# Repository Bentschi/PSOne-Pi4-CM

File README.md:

## Introduction
The goal of this project is to create open source hardware and software that replaces parts of a PSOne console mainly with a Raspbery PI 4 Compute Module, while remaining the beauty of the console and most of the functionality.
That means you would be able to use your playstation dualshock controllers, the memory card slots, and if i can get it to work the cd drive aswell.

## Raspberry Pi 4 Compute Module - the heart
As mentioned it will be mainly powered by a Raspberry PI 4 Compute Module, and i will try to break out as much IO as reasonably possible.
Sadly in a PSOne with a CD drive there is not much room to work with, and I decided for a non-destructive method of routing out the ports.
I want to use the connector U10-A074-361T from Amphenol (also known as Slim SAS, and used mostly in servers).
The connector is not really cheap and a little wider than the AV multi out.
But that is the price to pay to not destroy the case of the console, and if the connector is inset in the existing hole it will fit.
With that connector I will route dual HDMI, the gigabit network interface and USB 2.0 out of the back.
As a power port I will use a USB type C receptacle.
A cable that connects to that connector could look something like the following picture.

Alternatively a hub could be designed with said ports and maybe a few extras like usb hub and sound.

I will also add the barrel plug you find on a PSOne.
To save some cost and precious board space the Dual Shock function will most certainly only be enabled by using this barrel plug.
The original PSOne power supply (7.5V / 2.2A) seems to be enough to power this entire system (estimated-power-consumption.ods), however when using a M.2 SSD I would suggest to use a better power supply like the one for the Playstation 2 slim (8.5V / 5.6A).

The PCIe i want to use for a M.2 card interface. and i would love to split the pcie lane for USB 3.0 aswell, but then again i want to stay in a reasonable price range for the parts.
The M.2 slot will be able to hold up to 22x60mm cards, and for 22x80mm cards there would be about 7mm vertical clearance, since the only place where a M.2 slot would make sense interferes a little bit with the cd drive.
Sadly I needed more room for the internal power supply, so I had to remove the footprint (mounting hole) for 22x110mm cards.

I haven't managed to find a good place for a SD card holder, but i will route out the traces at least and put a footprint somewhere internally.
I will route out the DSI and CSI connectors aswell, even if i don't really see a use inside a console for them.

There will be an internal 4 port USB 2.0 hub from the PIs USB 2.0 interface.
One of these 4 USB lines will be routed through the Slim SAS connector.
2 of these USB 2.0 lines will be broken out to an internal 9-Pin USB Header, like you find on motherboards.
And the last USB 2.0 will be used to connect to a STM32F103 chip, that will interface the PSOne peripherals.

## STM32F103 - the PSOne interface
The intended use of the STM32F103 chip is to read from and write to the PSOne controller ports and memory card slots, and hopefully if i can get it to work the cd drive aswell.

The STM32F103 chip will communicate with the Raspberry PI Compute Module via USB 2.0 and will introduce itself as a compound device.
That means that only one USB line is required, and the STM32F103 will be recognized as multiple devices which would be 2x game controllers, 2x mass storage devices (the memory card slots), a cd drive, and probably a device that controls the PWMs for the power LED (RGB of course) and fan in the console.

I want to use a USB type C receptacle to power the console, and i have the idea that if the console is turned off or the Compute Module is not populated, and the console is plugged into a USB Host device (like a Computer), that the USB from the STM32F103 shall be passed through this USB type C connector, so that it is possible to use the PSOne peripherals on other devices aswell.

I am aware that CD drives are obsolete by todays standards, and that it is not gonna be that easy to interface the cd assembly, since there is no documentation about it or a standard like IDE or SATA used.
But for completeness i would want to have it working. And if i get it working it would be pretty simple to make it read actual Playstation CDs since the copy protection is not too complicated if you have full control over the entire CD assembly anyway.

## Cooling the Compute Module
Realisticly a flat fan like in laptops should probably be used and a shroud should be designed, that the air is taken from above the M.2 slot and pushed over the compute module, and with the shroud then directed to the bottom right vent holes on the console.
A connector for a fan (5V / 1A max), PWM controlled by the STM32 will be available, sharing one of the ULN2003 chips that are mainly used for the CD drive.

## Current status
I am currently working on the design and schematic for the board in KiCad.
I want to get as much done as possible until i order a PCB from that to test everything.

I want to mention that I have repaired a lot of older consoles in the past and I have very good knowledge of how these devices actually work.
And with all that knowledge, together with my very good programming skills, and my passion about old consoles and interrest in electronics, i think i have everything i need to get this project working.
But i have to say, even if i am aware of most of the design rules and guidelines, i have never designed a PCB before that i actually ordered to manufacture.
So this would be my very first.

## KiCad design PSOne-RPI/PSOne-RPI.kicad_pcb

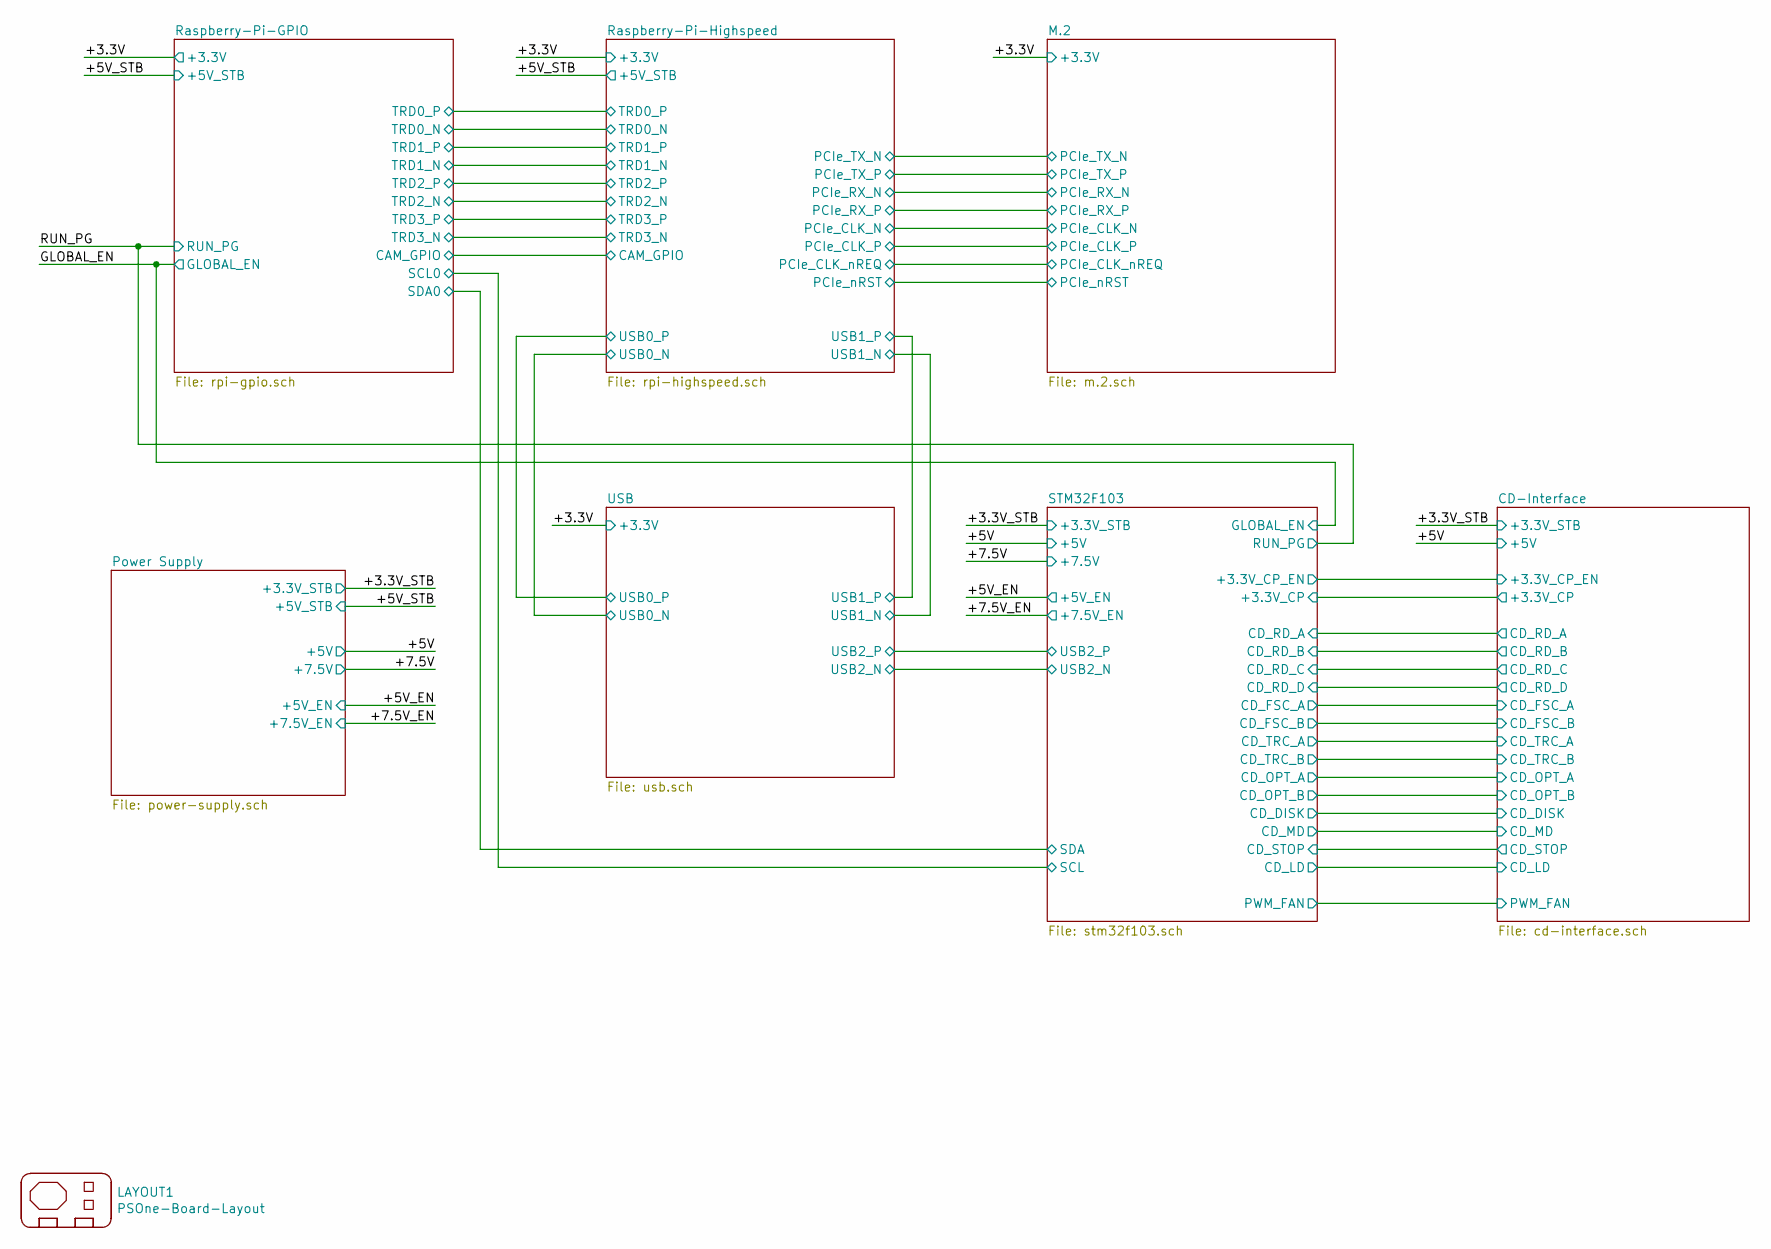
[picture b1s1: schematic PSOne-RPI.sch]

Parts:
LAYOUT1: PSOne-Board-Layout; PSOne-Layout

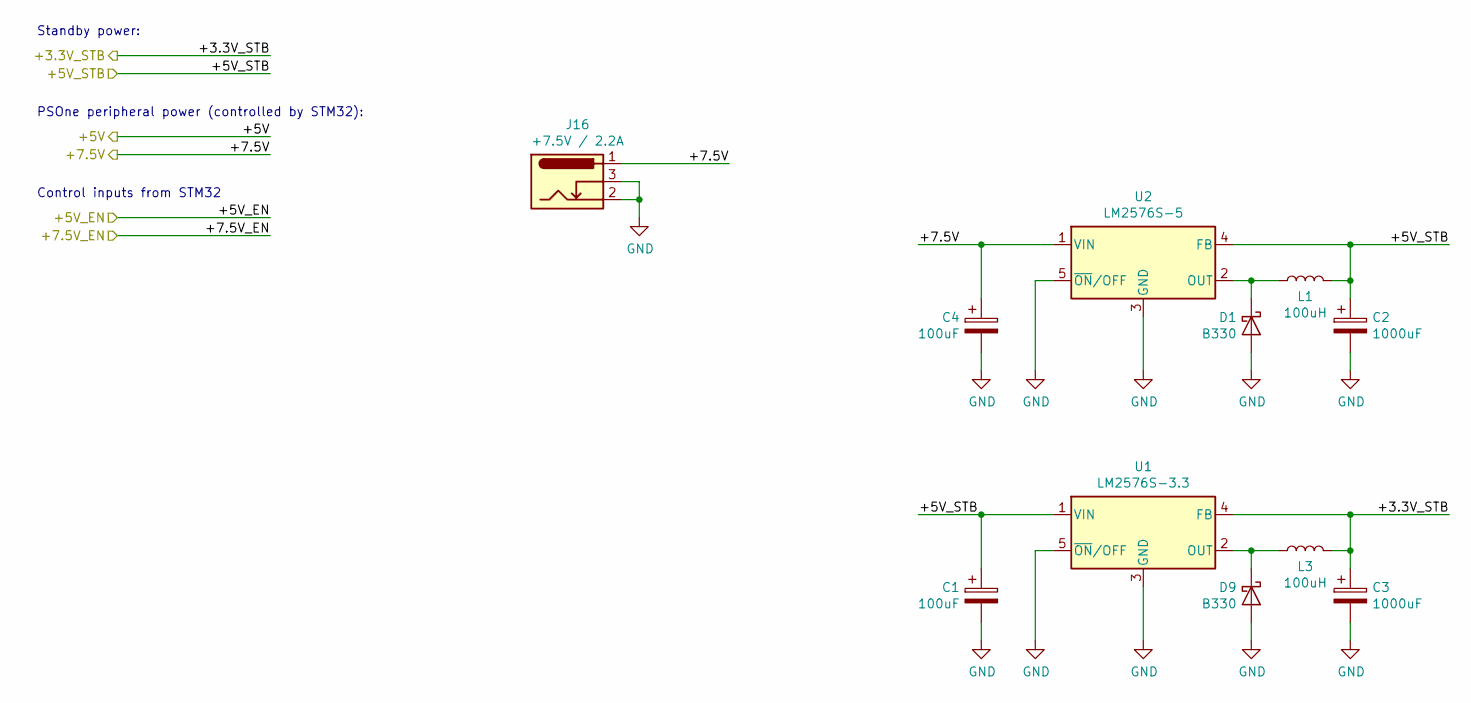
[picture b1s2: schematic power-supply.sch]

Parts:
C1, C4: 100uF; CP_Elec_6.3x5.8
C2, C3: 1000uF; CP_Elec_8x6.5
D1, D9: B330; D_SMC
J16: +7.5V / 2.2A; BarrelJack_Wuerth_6941xx301002
L1, L3: 100uH; L_Bourns_SRR1260
U1: LM2576S-3.3; TO-263-5_TabPin3
U2: LM2576S-5; TO-263-5_TabPin3

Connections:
/+3.3V_STB: C3.1, L3.2, U1.4 (FB); also elsewhere on the board
/+5V_STB: C1.1, C2.1, L1.2, U1.1 (VIN), U2.4 (FB); also elsewhere on the board
/+7.5V: C4.1, J16.1, U2.1 (VIN); also elsewhere on the board
GND: C1.2, C2.2, C3.2, C4.2, D1.2 (A), D9.2 (A), J16.2, J16.3, U1.3 (GND), U1.5 (~ON~/OFF), U2.3 (GND), U2.5 (~ON~/OFF); also elsewhere on the board
unnamed: D1.1 (K), L1.1, U2.2 (OUT)
unnamed: D9.1 (K), L3.1, U1.2 (OUT)

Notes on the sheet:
Standby power:
PSOne peripheral power (controlled by STM32):
Control inputs from STM32

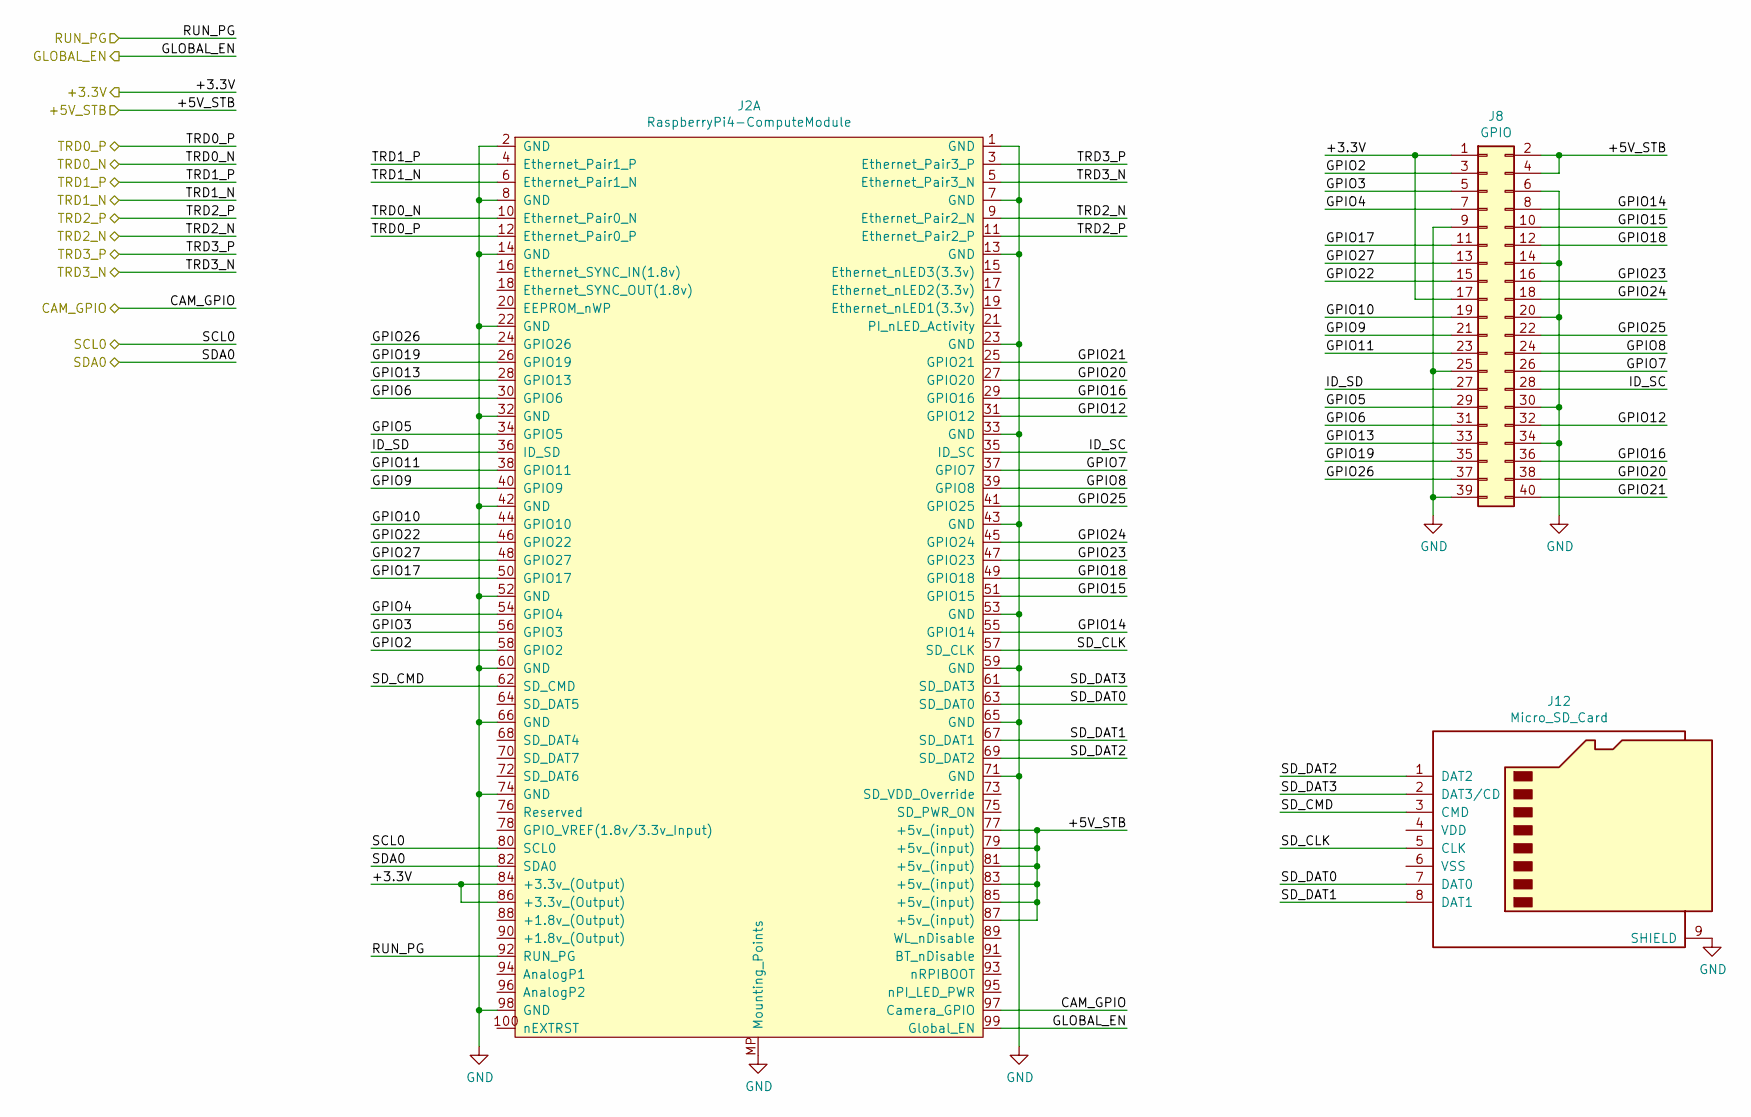
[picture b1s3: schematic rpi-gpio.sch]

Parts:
J2: RaspberryPi4-ComputeModule
J8: GPIO; PinHeader_2x20_P2.54mm_Vertical_SMD
J12: Micro_SD_Card; microSD_HC_Wuerth_693072010801

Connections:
/+3.3V: J2.84 (+3.3v_(Output)), J2.86 (+3.3v_(Output)), J8.1, J8.17; also elsewhere on the board
/+5V_STB: J2.77 (+5v_(input)), J2.79 (+5v_(input)), J2.81 (+5v_(input)), J2.83 (+5v_(input)), J2.85 (+5v_(input)), J2.87 (+5v_(input)), J8.2, J8.4; also elsewhere on the board
/GLOBAL_EN: J2.99 (Global_EN)
/RUN_PG: J2.92 (RUN_PG)
/Raspberry-Pi-GPIO/CAM_GPIO: J2.97 (Camera_GPIO); also elsewhere on the board
/Raspberry-Pi-GPIO/GPIO2: J2.58 (GPIO2), J8.3
/Raspberry-Pi-GPIO/GPIO3: J2.56 (GPIO3), J8.5
/Raspberry-Pi-GPIO/GPIO4: J2.54 (GPIO4), J8.7
/Raspberry-Pi-GPIO/GPIO5: J2.34 (GPIO5), J8.29
/Raspberry-Pi-GPIO/GPIO6: J2.30 (GPIO6), J8.31
/Raspberry-Pi-GPIO/GPIO7: J2.37 (GPIO7), J8.26
/Raspberry-Pi-GPIO/GPIO8: J2.39 (GPIO8), J8.24
/Raspberry-Pi-GPIO/GPIO9: J2.40 (GPIO9), J8.21
/Raspberry-Pi-GPIO/GPIO10: J2.44 (GPIO10), J8.19
/Raspberry-Pi-GPIO/GPIO11: J2.38 (GPIO11), J8.23
/Raspberry-Pi-GPIO/GPIO12: J2.31 (GPIO12), J8.32
/Raspberry-Pi-GPIO/GPIO13: J2.28 (GPIO13), J8.33
/Raspberry-Pi-GPIO/GPIO14: J2.55 (GPIO14), J8.8
/Raspberry-Pi-GPIO/GPIO15: J2.51 (GPIO15), J8.10
/Raspberry-Pi-GPIO/GPIO16: J2.29 (GPIO16), J8.36
/Raspberry-Pi-GPIO/GPIO17: J2.50 (GPIO17), J8.11
/Raspberry-Pi-GPIO/GPIO18: J2.49 (GPIO18), J8.12
/Raspberry-Pi-GPIO/GPIO19: J2.26 (GPIO19), J8.35
/Raspberry-Pi-GPIO/GPIO20: J2.27 (GPIO20), J8.38
/Raspberry-Pi-GPIO/GPIO21: J2.25 (GPIO21), J8.40
/Raspberry-Pi-GPIO/GPIO22: J2.46 (GPIO22), J8.15
/Raspberry-Pi-GPIO/GPIO23: J2.47 (GPIO23), J8.16
/Raspberry-Pi-GPIO/GPIO24: J2.45 (GPIO24), J8.18
/Raspberry-Pi-GPIO/GPIO25: J2.41 (GPIO25), J8.22
/Raspberry-Pi-GPIO/GPIO26: J2.24 (GPIO26), J8.37
/Raspberry-Pi-GPIO/GPIO27: J2.48 (GPIO27), J8.13
/Raspberry-Pi-GPIO/ID_SC: J2.35 (ID_SC), J8.28
/Raspberry-Pi-GPIO/ID_SD: J2.36 (ID_SD), J8.27
/Raspberry-Pi-GPIO/SD_CLK: J2.57 (SD_CLK), J12.5 (CLK)
/Raspberry-Pi-GPIO/SD_CMD: J2.62 (SD_CMD), J12.3 (CMD)
/Raspberry-Pi-GPIO/SD_DAT0: J2.63 (SD_DAT0), J12.7 (DAT0)
/Raspberry-Pi-GPIO/SD_DAT1: J2.67 (SD_DAT1), J12.8 (DAT1)
/Raspberry-Pi-GPIO/SD_DAT2: J2.69 (SD_DAT2), J12.1 (DAT2)
/Raspberry-Pi-GPIO/SD_DAT3: J2.61 (SD_DAT3), J12.2 (DAT3/CD)
/Raspberry-Pi-GPIO/TRD0_N: J2.10 (Ethernet_Pair0_N); also elsewhere on the board
/Raspberry-Pi-GPIO/TRD0_P: J2.12 (Ethernet_Pair0_P); also elsewhere on the board
/Raspberry-Pi-GPIO/TRD1_N: J2.6 (Ethernet_Pair1_N); also elsewhere on the board
/Raspberry-Pi-GPIO/TRD1_P: J2.4 (Ethernet_Pair1_P); also elsewhere on the board
/Raspberry-Pi-GPIO/TRD2_N: J2.9 (Ethernet_Pair2_N); also elsewhere on the board
/Raspberry-Pi-GPIO/TRD2_P: J2.11 (Ethernet_Pair2_P); also elsewhere on the board
/Raspberry-Pi-GPIO/TRD3_N: J2.5 (Ethernet_Pair3_N); also elsewhere on the board
/Raspberry-Pi-GPIO/TRD3_P: J2.3 (Ethernet_Pair3_P); also elsewhere on the board
/STM32F103/SCL: J2.80 (SCL0); also elsewhere on the board
/STM32F103/SDA: J2.82 (SDA0); also elsewhere on the board
GND: J2.1 (GND), J2.2 (GND), J2.7 (GND), J2.8 (GND), J2.13 (GND), J2.14 (GND), J2.22 (GND), J2.23 (GND), J2.32 (GND), J2.33 (GND), J2.42 (GND), J2.43 (GND), J2.52 (GND), J2.53 (GND), J2.59 (GND), J2.60 (GND), J2.65 (GND), J2.66 (GND), J2.71 (GND), J2.74 (GND), J2.98 (GND), J2.MP (Mounting_Points), J8.6, J8.9, J8.14, J8.20, J8.25, J8.30, J8.34, J8.39, J12.9 (SHIELD); also elsewhere on the board

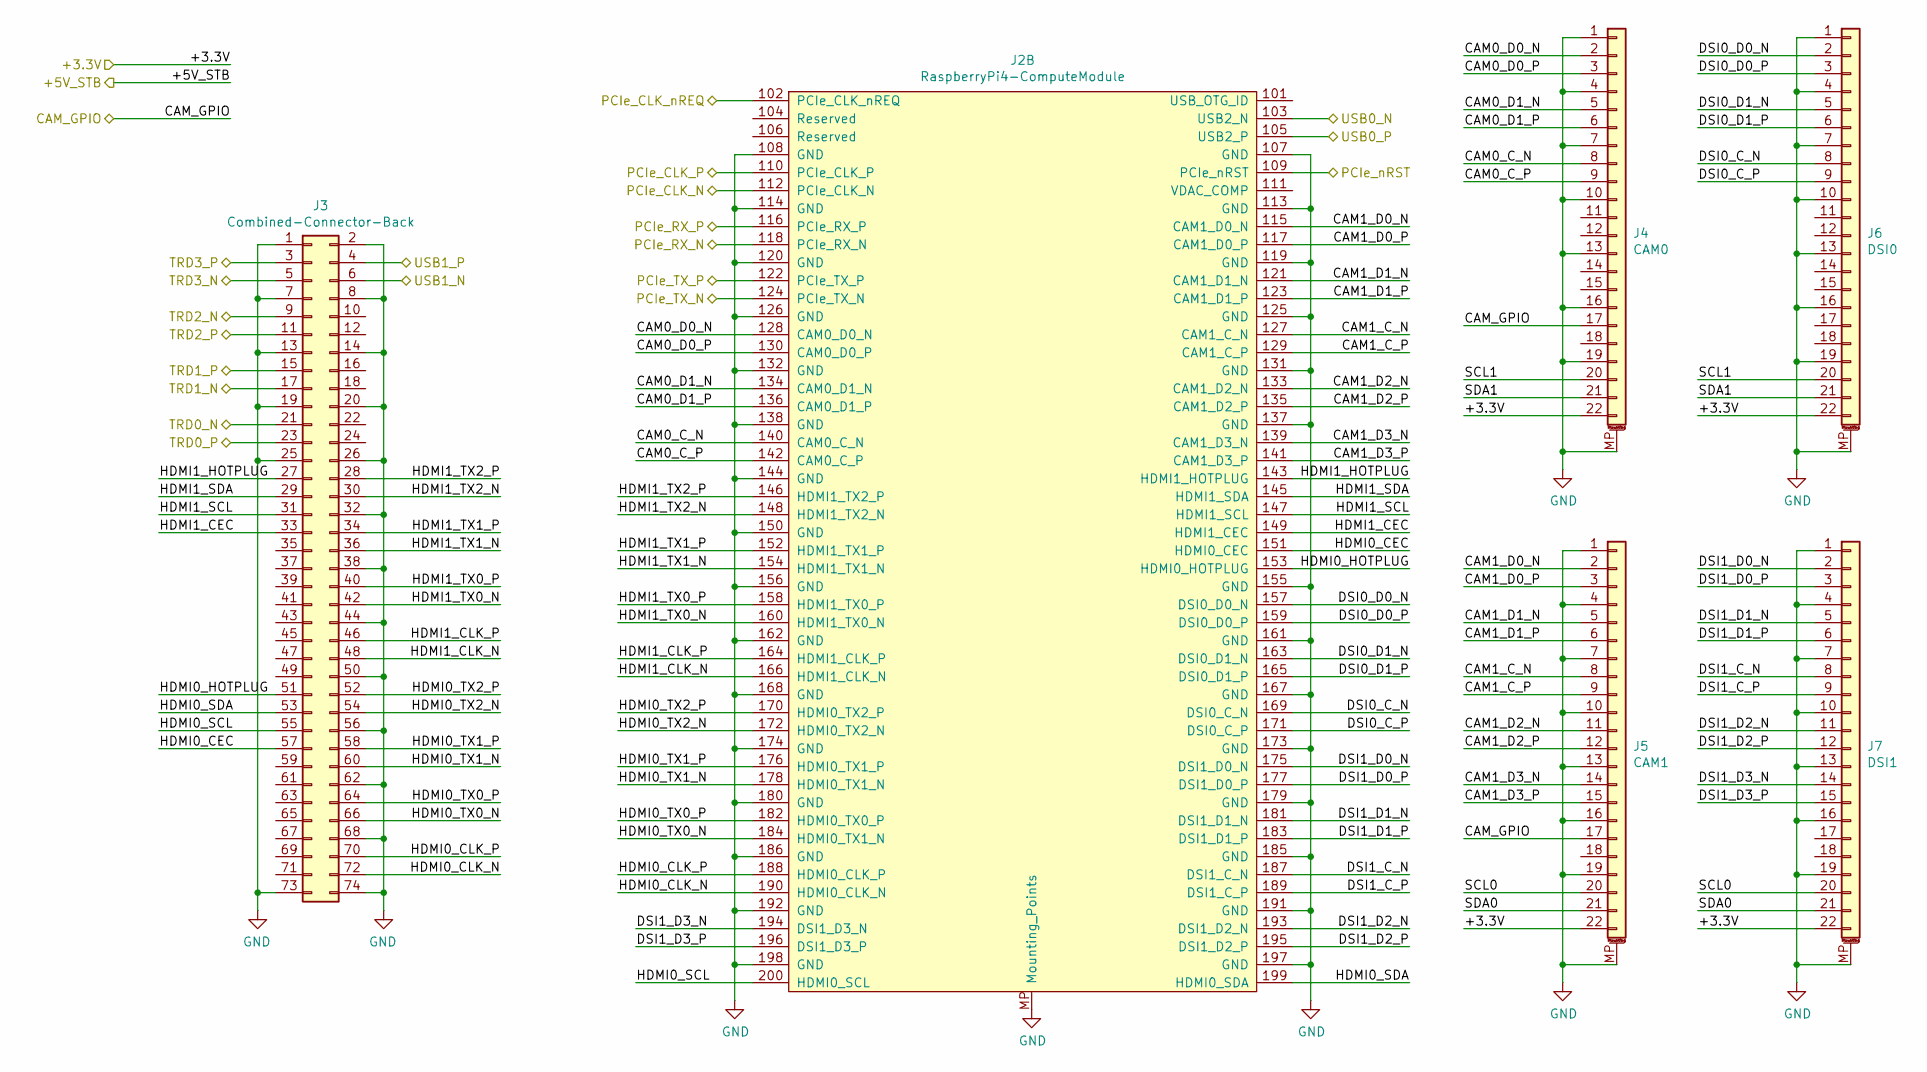
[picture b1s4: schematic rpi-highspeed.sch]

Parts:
J2: RaspberryPi4-ComputeModule
J3: Combined-Connector-Back; U10-A074-361T
J4: CAM0; TE_2-1734839-2_1x22-1MP_P0.5mm_Horizontal
J5: CAM1; TE_2-1734839-2_1x22-1MP_P0.5mm_Horizontal
J6: DSI0; TE_2-1734839-2_1x22-1MP_P0.5mm_Horizontal
J7: DSI1; TE_2-1734839-2_1x22-1MP_P0.5mm_Horizontal

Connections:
/+3.3V: J4.22, J5.22, J6.22, J7.22; also elsewhere on the board
/M.2/PCIe_CLK_N: J2.112 (PCIe_CLK_N); also elsewhere on the board
/M.2/PCIe_CLK_P: J2.110 (PCIe_CLK_P); also elsewhere on the board
/M.2/PCIe_CLK_nREQ: J2.102 (PCIe_CLK_nREQ); also elsewhere on the board
/M.2/PCIe_RX_N: J2.118 (PCIe_RX_N); also elsewhere on the board
/M.2/PCIe_RX_P: J2.116 (PCIe_RX_P); also elsewhere on the board
/M.2/PCIe_TX_N: J2.124 (PCIe_TX_N); also elsewhere on the board
/M.2/PCIe_TX_P: J2.122 (PCIe_TX_P); also elsewhere on the board
/M.2/PCIe_nRST: J2.109 (PCIe_nRST); also elsewhere on the board
/Raspberry-Pi-GPIO/CAM_GPIO: J4.17, J5.17; also elsewhere on the board
/Raspberry-Pi-GPIO/TRD0_N: J3.21; also elsewhere on the board
/Raspberry-Pi-GPIO/TRD0_P: J3.23; also elsewhere on the board
/Raspberry-Pi-GPIO/TRD1_N: J3.17; also elsewhere on the board
/Raspberry-Pi-GPIO/TRD1_P: J3.15; also elsewhere on the board
/Raspberry-Pi-GPIO/TRD2_N: J3.9; also elsewhere on the board
/Raspberry-Pi-GPIO/TRD2_P: J3.11; also elsewhere on the board
/Raspberry-Pi-GPIO/TRD3_N: J3.5; also elsewhere on the board
/Raspberry-Pi-GPIO/TRD3_P: J3.3; also elsewhere on the board
/Raspberry-Pi-Highspeed/CAM0_C_N: J2.140 (CAM0_C_N), J4.8
/Raspberry-Pi-Highspeed/CAM0_C_P: J2.142 (CAM0_C_P), J4.9
/Raspberry-Pi-Highspeed/CAM0_D0_N: J2.128 (CAM0_D0_N), J4.2
/Raspberry-Pi-Highspeed/CAM0_D0_P: J2.130 (CAM0_D0_P), J4.3
/Raspberry-Pi-Highspeed/CAM0_D1_N: J2.134 (CAM0_D1_N), J4.5
/Raspberry-Pi-Highspeed/CAM0_D1_P: J2.136 (CAM0_D1_P), J4.6
/Raspberry-Pi-Highspeed/CAM1_C_N: J2.127 (CAM1_C_N), J5.8
/Raspberry-Pi-Highspeed/CAM1_C_P: J2.129 (CAM1_C_P), J5.9
/Raspberry-Pi-Highspeed/CAM1_D0_N: J2.115 (CAM1_D0_N), J5.2
/Raspberry-Pi-Highspeed/CAM1_D0_P: J2.117 (CAM1_D0_P), J5.3
/Raspberry-Pi-Highspeed/CAM1_D1_N: J2.121 (CAM1_D1_N), J5.5
/Raspberry-Pi-Highspeed/CAM1_D1_P: J2.123 (CAM1_D1_P), J5.6
/Raspberry-Pi-Highspeed/CAM1_D2_N: J2.133 (CAM1_D2_N), J5.11
/Raspberry-Pi-Highspeed/CAM1_D2_P: J2.135 (CAM1_D2_P), J5.12
/Raspberry-Pi-Highspeed/CAM1_D3_N: J2.139 (CAM1_D3_N), J5.14
/Raspberry-Pi-Highspeed/CAM1_D3_P: J2.141 (CAM1_D3_P), J5.15
/Raspberry-Pi-Highspeed/DSI0_C_N: J2.169 (DSI0_C_N), J6.8
/Raspberry-Pi-Highspeed/DSI0_C_P: J2.171 (DSI0_C_P), J6.9
/Raspberry-Pi-Highspeed/DSI0_D0_N: J2.157 (DSI0_D0_N), J6.2
/Raspberry-Pi-Highspeed/DSI0_D0_P: J2.159 (DSI0_D0_P), J6.3
/Raspberry-Pi-Highspeed/DSI0_D1_N: J2.163 (DSI0_D1_N), J6.5
/Raspberry-Pi-Highspeed/DSI0_D1_P: J2.165 (DSI0_D1_P), J6.6
/Raspberry-Pi-Highspeed/DSI1_C_N: J2.187 (DSI1_C_N), J7.8
/Raspberry-Pi-Highspeed/DSI1_C_P: J2.189 (DSI1_C_P), J7.9
/Raspberry-Pi-Highspeed/DSI1_D0_N: J2.175 (DSI1_D0_N), J7.2
/Raspberry-Pi-Highspeed/DSI1_D0_P: J2.177 (DSI1_D0_P), J7.3
/Raspberry-Pi-Highspeed/DSI1_D1_N: J2.181 (DSI1_D1_N), J7.5
/Raspberry-Pi-Highspeed/DSI1_D1_P: J2.183 (DSI1_D1_P), J7.6
/Raspberry-Pi-Highspeed/DSI1_D2_N: J2.193 (DSI1_D2_N), J7.11
/Raspberry-Pi-Highspeed/DSI1_D2_P: J2.195 (DSI1_D2_P), J7.12
/Raspberry-Pi-Highspeed/DSI1_D3_N: J2.194 (DSI1_D3_N), J7.14
/Raspberry-Pi-Highspeed/DSI1_D3_P: J2.196 (DSI1_D3_P), J7.15
/Raspberry-Pi-Highspeed/HDMI0_CEC: J2.151 (HDMI0_CEC), J3.57
/Raspberry-Pi-Highspeed/HDMI0_CLK_N: J2.190 (HDMI0_CLK_N), J3.72
/Raspberry-Pi-Highspeed/HDMI0_CLK_P: J2.188 (HDMI0_CLK_P), J3.70
/Raspberry-Pi-Highspeed/HDMI0_HOTPLUG: J2.153 (HDMI0_HOTPLUG), J3.51
/Raspberry-Pi-Highspeed/HDMI0_SCL: J2.200 (HDMI0_SCL), J3.55
/Raspberry-Pi-Highspeed/HDMI0_SDA: J2.199 (HDMI0_SDA), J3.53
/Raspberry-Pi-Highspeed/HDMI0_TX0_N: J2.184 (HDMI0_TX1_N), J3.66
/Raspberry-Pi-Highspeed/HDMI0_TX0_P: J2.182 (HDMI0_TX0_P), J3.64
/Raspberry-Pi-Highspeed/HDMI0_TX1_N: J2.178 (HDMI0_TX1_N), J3.60
/Raspberry-Pi-Highspeed/HDMI0_TX1_P: J2.176 (HDMI0_TX1_P), J3.58
/Raspberry-Pi-Highspeed/HDMI0_TX2_N: J2.172 (HDMI0_TX2_N), J3.54
/Raspberry-Pi-Highspeed/HDMI0_TX2_P: J2.170 (HDMI0_TX2_P), J3.52
/Raspberry-Pi-Highspeed/HDMI1_CEC: J2.149 (HDMI1_CEC), J3.33
/Raspberry-Pi-Highspeed/HDMI1_CLK_N: J2.166 (HDMI1_CLK_N), J3.48
/Raspberry-Pi-Highspeed/HDMI1_CLK_P: J2.164 (HDMI1_CLK_P), J3.46
/Raspberry-Pi-Highspeed/HDMI1_HOTPLUG: J2.143 (HDMI1_HOTPLUG), J3.27
/Raspberry-Pi-Highspeed/HDMI1_SCL: J2.147 (HDMI1_SCL), J3.31
/Raspberry-Pi-Highspeed/HDMI1_SDA: J2.145 (HDMI1_SDA), J3.29
/Raspberry-Pi-Highspeed/HDMI1_TX0_N: J2.160 (HDMI1_TX0_N), J3.42
/Raspberry-Pi-Highspeed/HDMI1_TX0_P: J2.158 (HDMI1_TX0_P), J3.40
/Raspberry-Pi-Highspeed/HDMI1_TX1_N: J2.154 (HDMI1_TX1_N), J3.36
/Raspberry-Pi-Highspeed/HDMI1_TX1_P: J2.152 (HDMI1_TX1_P), J3.34
/Raspberry-Pi-Highspeed/HDMI1_TX2_N: J2.148 (HDMI1_TX2_N), J3.30
/Raspberry-Pi-Highspeed/HDMI1_TX2_P: J2.146 (HDMI1_TX2_P), J3.28
/Raspberry-Pi-Highspeed/SCL0: J5.20, J7.20
/Raspberry-Pi-Highspeed/SCL1: J4.20, J6.20
/Raspberry-Pi-Highspeed/SDA0: J5.21, J7.21
/Raspberry-Pi-Highspeed/SDA1: J4.21, J6.21
/Raspberry-Pi-Highspeed/USB0_N: J2.103 (USB2_N); also elsewhere on the board
/Raspberry-Pi-Highspeed/USB0_P: J2.105 (USB2_P); also elsewhere on the board
/Raspberry-Pi-Highspeed/USB1_N: J3.6; also elsewhere on the board
/Raspberry-Pi-Highspeed/USB1_P: J3.4; also elsewhere on the board
GND: J2.107 (GND), J2.108 (GND), J2.113 (GND), J2.114 (GND), J2.119 (GND), J2.120 (GND), J2.125 (GND), J2.126 (GND), J2.131 (GND), J2.132 (GND), J2.137 (GND), J2.138 (GND), J2.144 (GND), J2.150 (GND), J2.155 (GND), J2.156 (GND), J2.161 (GND), J2.162 (GND), J2.167 (GND), J2.168 (GND), J2.173 (GND), J2.174 (GND), J2.179 (GND), J2.180 (GND), J2.185 (GND), J2.186 (GND), J2.191 (GND), J2.192 (GND), J2.197 (GND), J2.198 (GND), J2.MP (Mounting_Points), J3.1, J3.2, J3.7, J3.8, J3.13, J3.14, J3.19, J3.20, J3.25, J3.26, J3.32, J3.38, J3.44, J3.50, J3.56, J3.62, J3.68, J3.73, J3.74, J4.1, J4.4, J4.7, J4.10, J4.13, J4.16, J4.19, J4.MP (MountPin), J5.1, J5.4, J5.7, J5.10, J5.13, J5.16, J5.19, J5.MP (MountPin), J6.1, J6.4, J6.7, J6.10, J6.13, J6.16, J6.19, J6.MP (MountPin), J7.1, J7.4, J7.7, J7.10, J7.13, J7.16, J7.19, J7.MP (MountPin); also elsewhere on the board

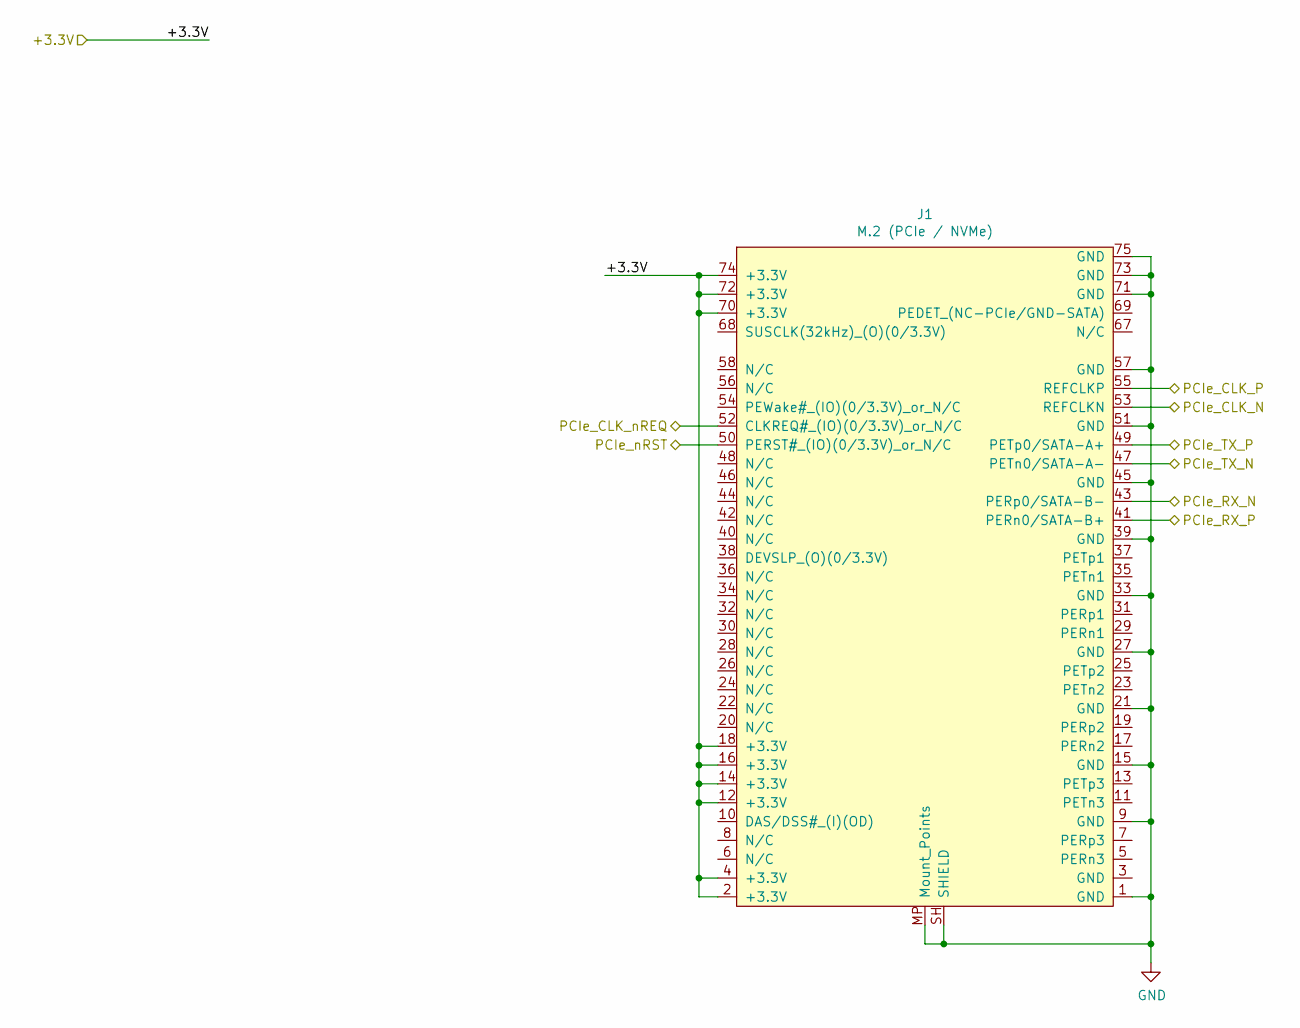
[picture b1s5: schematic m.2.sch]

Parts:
J1: M.2 (PCIe / NVMe); M.2_Connector

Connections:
/+3.3V: J1.2 (+3.3V), J1.4 (+3.3V), J1.12 (+3.3V), J1.14 (+3.3V), J1.16 (+3.3V), J1.18 (+3.3V), J1.70 (+3.3V), J1.72 (+3.3V), J1.74 (+3.3V); also elsewhere on the board
/M.2/PCIe_CLK_N: J1.53 (REFCLKN); also elsewhere on the board
/M.2/PCIe_CLK_P: J1.55 (REFCLKP); also elsewhere on the board
/M.2/PCIe_CLK_nREQ: J1.52 (CLKREQ#_(IO)(0/3.3V)_or_N/C); also elsewhere on the board
/M.2/PCIe_RX_N: J1.43 (PERp0/SATA-B-); also elsewhere on the board
/M.2/PCIe_RX_P: J1.41 (PERn0/SATA-B+); also elsewhere on the board
/M.2/PCIe_TX_N: J1.47 (PETn0/SATA-A-); also elsewhere on the board
/M.2/PCIe_TX_P: J1.49 (PETp0/SATA-A+); also elsewhere on the board
/M.2/PCIe_nRST: J1.50 (PERST#_(IO)(0/3.3V)_or_N/C); also elsewhere on the board
GND: J1.1 (GND), J1.9 (GND), J1.15 (GND), J1.21 (GND), J1.27 (GND), J1.33 (GND), J1.39 (GND), J1.45 (GND), J1.51 (GND), J1.57 (GND), J1.71 (GND), J1.73 (GND), J1.75 (GND), J1.MP (Mount_Points), J1.SH (SHIELD); also elsewhere on the board

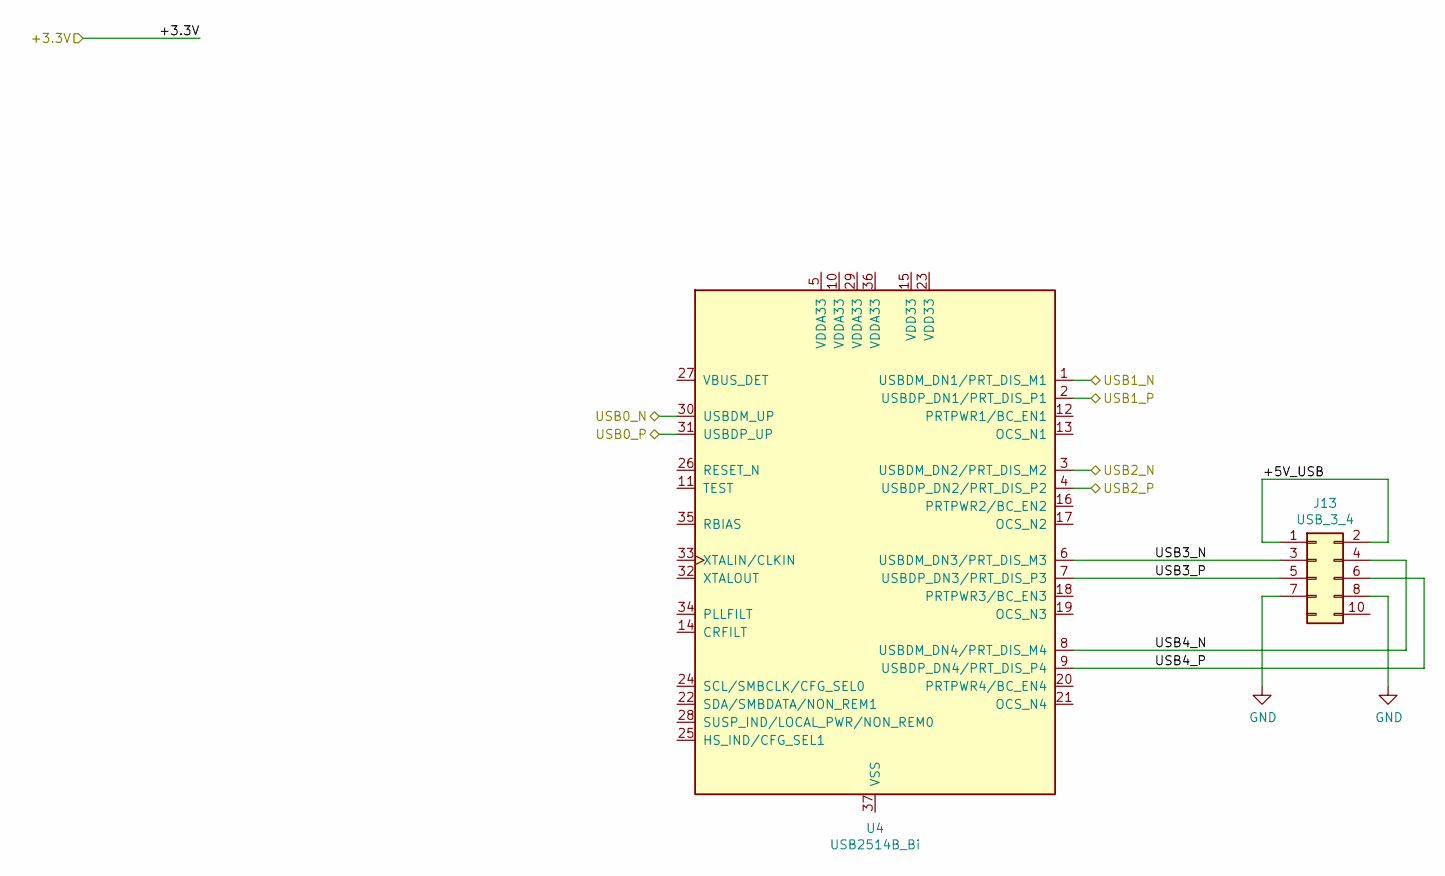
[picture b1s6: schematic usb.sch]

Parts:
J13: USB_3_4; PinHeader_2xUSB2_P2.54mm_Vertical_SMD
U4: USB2514B_Bi; QFN-36-1EP_6x6mm_P0.5mm_EP3.7x3.7mm

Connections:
/Raspberry-Pi-Highspeed/USB0_N: U4.30 (USBDM_UP); also elsewhere on the board
/Raspberry-Pi-Highspeed/USB0_P: U4.31 (USBDP_UP); also elsewhere on the board
/Raspberry-Pi-Highspeed/USB1_N: U4.1 (USBDM_DN1/PRT_DIS_M1); also elsewhere on the board
/Raspberry-Pi-Highspeed/USB1_P: U4.2 (USBDP_DN1/PRT_DIS_P1); also elsewhere on the board
/STM32F103/USB2_N: U4.3 (USBDM_DN2/PRT_DIS_M2); also elsewhere on the board
/STM32F103/USB2_P: U4.4 (USBDP_DN2/PRT_DIS_P2); also elsewhere on the board
/USB/+5V_USB: J13.1, J13.2
/USB/USB3_N: J13.3, U4.6 (USBDM_DN3/PRT_DIS_M3)
/USB/USB3_P: J13.5, U4.7 (USBDP_DN3/PRT_DIS_P3)
/USB/USB4_N: J13.4, U4.8 (USBDM_DN4/PRT_DIS_M4)
/USB/USB4_P: J13.6, U4.9 (USBDP_DN4/PRT_DIS_P4)
GND: J13.7, J13.8; also elsewhere on the board
